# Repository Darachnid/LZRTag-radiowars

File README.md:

# [LZRTag](https://hackaday.io/project/160804-lzrtag-flexible-diy-lasertag)

### ESP32-Based Lasertag

Ever wanted to set up your own system of Lasertag?
Interested in having an easily modifiable system to create your own gamemodes and styles with?
Or just looking for a cool project to try out?
Well, why not take a spin at this!

*Note:* This project is not in serious development. I (Xasin) take no responsibility for what is done with this code, and I can't guarantee it'll do exactly what I tell it to (even if I try to give it treats >:c)
However, it is a fully functional system, if you know how to use it, and it has proven itself
to be pretty reliable and useful!

## The components
In order to have a functional game, you will need at least the following:
- Two or more soldered Lasertag Sets
- A WiFi access point or a newtwork of points throughout the arena.
- A MQTT Server, preferrably in the local network, to reduce ping.
- And a system running Ruby 2.4 or better, to run the Lasertag Backend and your gamemodes

## The Electronics
*Attention:* The electronics aren't necessarily beginner-friendly. I've designed them with components no smaller than a TSOP package or a 0805 resistor, but the newer versions of the hardware do include two QFN Packages - one for a optional IMU, so it can be left out, and one for a standard I2S audio chip, for which you can use any breakout board that supports 44100Hz, 16 bit playback. If you have a hot air gun,
definitely make use of it!

The electronics are based around the ESP32, a fairly cheap, powerful, WiFi and Bluetooth capable chip. The PCB includes all necessary support structures, including a battery charge circuit and a USB to UART converter to reprogram and debug the ESP.
It comes with the following hardware:
- The ESP32 plus beefy voltage regulation, ESD protection, etc. It ain't gonna break!
- A MAX I2S decoder + amplifier, for on-board, high quality audio.
- A LSM6D IMU, to detect movement, collisions, gestures, etc.
- Peripherals to receive and send IR Signals (documented here: TODO)
- Feedback in the shape of WS2812 LEDs and a vibration motor
- Trigger, Gun Select and Reload buttons.

The vest connection is exposed with a D-SUB connector, and I2C lines are available to make
more complex add-ons easier to achieve. There's also a I2C breakout connection on the PCB itself!

The Vest itself can be as simple as a couple of Vishay 40kHz IR receivers and WS2812 LEDs, but
there is a connection for vest-specific haptic feedback, and via the I2C connection it's easy to add
more complex features.

To solder one, check out the Aisler project here: https://aisler.net/p/QLILZEMV
Or head to the "Electronics" folder and generate your own Gerber files!

## The Casing
The 3D printed casing I designed is totally optional - the electronics can be easily fitted into any other casing, provided it has space for a switch, a speaker and a couple of LEDs!
However, if you do want to print it out, there's the Fusion360 page here: https://a360.co/2Lbm2zJ

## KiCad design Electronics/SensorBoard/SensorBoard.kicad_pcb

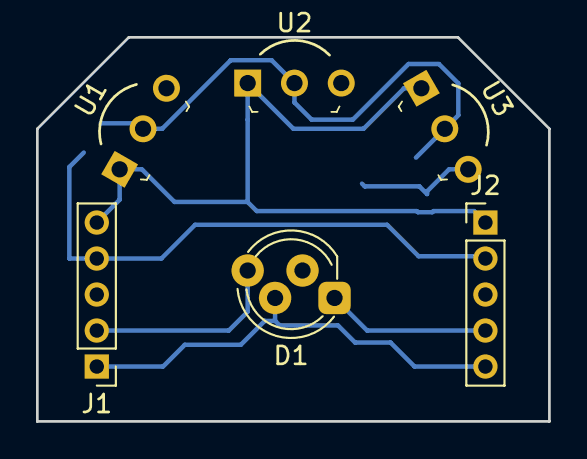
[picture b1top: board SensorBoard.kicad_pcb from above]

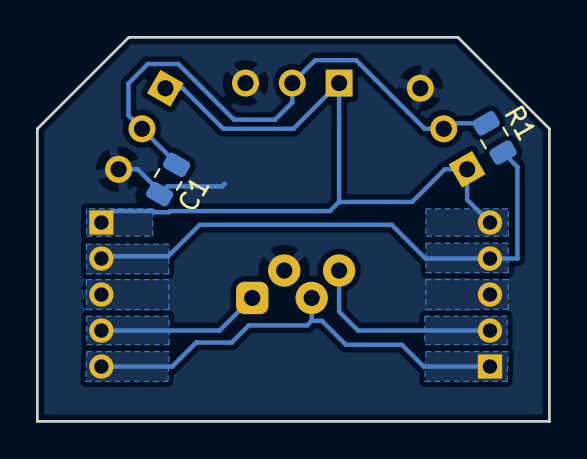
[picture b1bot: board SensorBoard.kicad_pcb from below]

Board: 2 copper layers, 28.4 x 21.3 mm, 8 parts (2 on the bottom side), 7 nets.

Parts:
C1: C_Small; C_0805_2012Metric
D1: NeoPixel_THT; LED_D5.0mm-4_RGB_Staggered_Pins
J1, J2: Conn_01x05_Male; PinHeader_1x05_P2.00mm_Vertical
R1: R_Small; R_0805_2012Metric
U1, U2, U3: TSSP58038; TO-92-3_Formed_Leads

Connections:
+3V3: J1.4, J2.2, R1.2
+BATT: D1.3, J1.1, J2.5
GND: C1.2, D1.2, J1.3, J2.3, U1.3, U2.3, U3.3
unnamed: C1.1, R1.1, U1.2, U2.2, U3.2
unnamed: D1.1, J2.4
unnamed: D1.4, J1.2
unnamed: J1.5, J2.1, U1.1, U2.1, U3.1

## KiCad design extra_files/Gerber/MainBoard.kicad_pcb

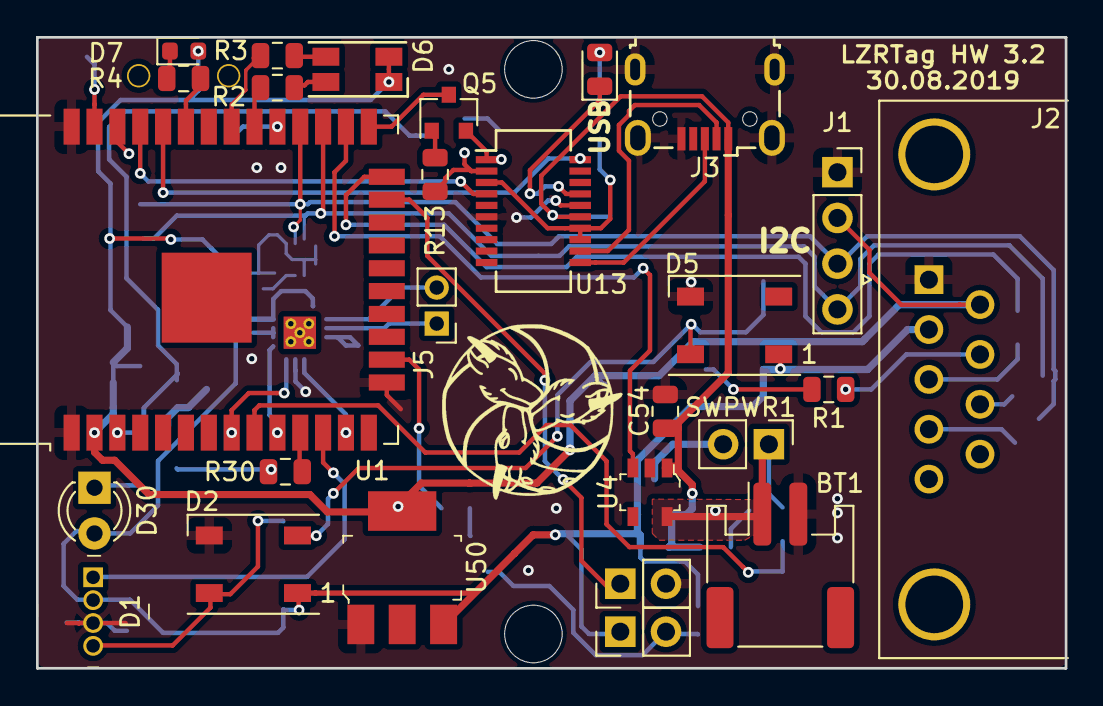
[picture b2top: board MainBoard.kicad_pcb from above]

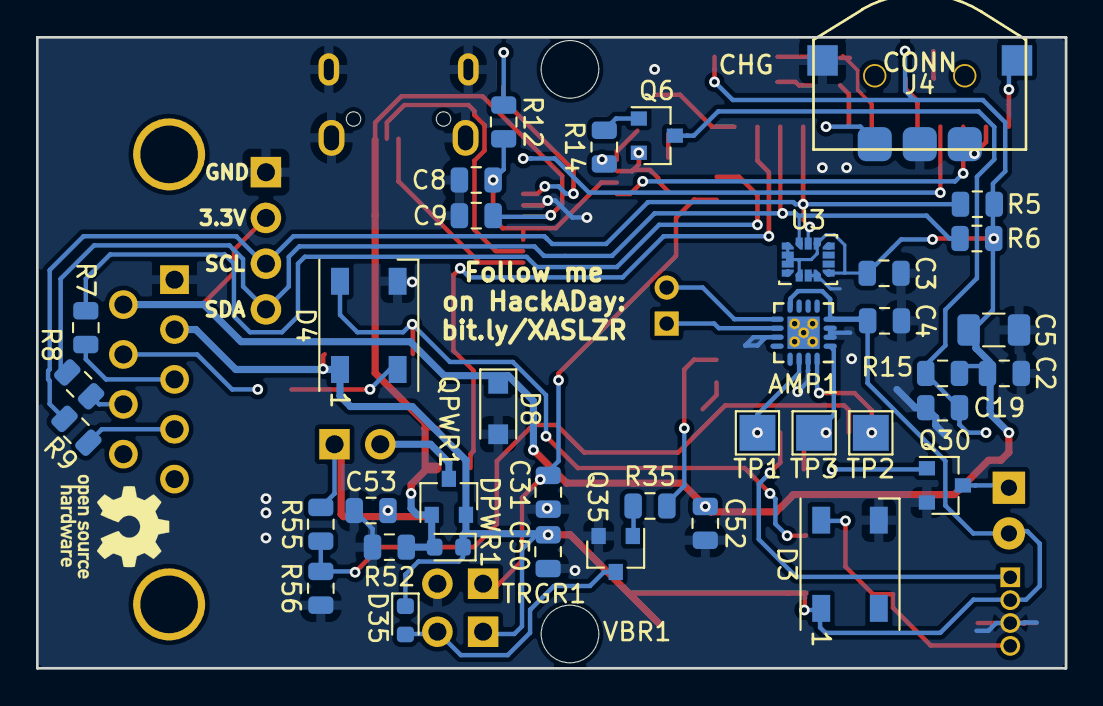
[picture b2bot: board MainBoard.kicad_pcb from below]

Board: 2 copper layers, 57.2 x 35.1 mm, 70 parts (40 on the bottom side), 53 nets.

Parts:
AMP1: MAX98357A; QFN-16-1EP_3x3mm_P0.5mm_EP2.7x2.7mm_ThermalVias
BT1: Battery_Cell; JST_PH_S2B-PH-SM4-TB_1x02-1MP_P2.00mm_Horizontal
C2, C8, C31: 150nF; C_0805_2012Metric
C3: 0.1uF; C_0805_2012Metric
C4, C9, C52, C53: 10uF; C_0805_2012Metric
C5: 47uF; C_1206_3216Metric
C19: 100nF; C_0805_2012Metric
C50, C54: 1uF; C_0805_2012Metric
D1: COM-12999; LED_RGB_WP154A4SUREQBFZGC
D2, D3, D4, D5: WS2812B; LED_WS2812B_PLCC4_5.0x5.0mm_P3.2mm
D6: LED_Dual_AACC; LED_RGB_1210
D7: LED; LED_0603_1608Metric
D8: D_Zener_ALT; D_SOD-123F
D30: SFH4346; LED_D3.0mm_IRBlack
D35: D_Schottky; D_0603_1608Metric
DPWR1: D_Schottky; D_0603_1608Metric
DUSB1: LED; LED_0805_2012Metric
H1, H2: MountingHole; MountingHole_3.2mm_M3_DIN965
H3: MountingHole; KiCad-Logo_5mm_SolderMask
H4: MountingHole; OSHW-Logo_5.7x6mm_SilkScreen
H6: MountingHole; DragonIcon
J1: Conn_01x04_Female; PinSocket_1x04_P2.54mm_Vertical
J2: DB9_Female; DSUB-9_Female_Horizontal_P2.77x2.84mm_EdgePinOffset4.94mm_H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
J3: USB_B_Micro; USB_Micro-B_Wuerth_629105150521
J4: Conn_01x04_Male; nav_switch_COM_08184
J5: Conn_01x02_Male; PinHeader_1x02_P2.00mm_Vertical
Q5, Q6: Q_NPN_BEC; SOT-23
Q30, Q35: PMBT2222A; SOT-23
QPWR1: IRLML6402; SOT-23
R1, R4, R7, R8, R9, R12, R30: 220; R_0805_2012Metric
R2, R3: 220R; R_0805_2012Metric
R5, R6, R35: 2.2k; R_0805_2012Metric
R13, R14, R15: R_Small; R_0805_2012Metric
R52: 10k; R_0805_2012Metric
R55: 100k; R_0805_2012Metric
R56: 200k; R_0805_2012Metric
SWPWR1: SW_SPST; PinHeader_1x02_P2.54mm_Vertical
TP1, TP2, TP3: TestPoint; TestPoint_Pad_2.0x2.0mm
TRGR1: SW_Push; PinHeader_1x02_P2.54mm_Vertical
U1: ESP32-WROOM-32
U3: LSM6DS3; LGA-14_3x2.5mm_P0.5mm_LayoutBorder3x4y
U4: MAX1555EZK_T; SOT-753
U13: FT231XS; SSOP-20_3.9x8.7mm_P0.635mm
U50: AP2114H-3_3TRG1; SOT-223
VBR1: Motor_DC_ALT; PinHeader_1x02_P2.54mm_Vertical

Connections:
+3V3: C2.1, C3.2, C5.2, C52.1, D6.1, D6.2, D7.2, D8.1, J1.2, J2.6, R5.1, R6.1, R15.1, U1.2, U3.1, U3.2, U3.3, U3.5, U3.8, U3.12, U50.4
+BATT: AMP1.4, AMP1.8, C4.1, C50.1, D1.2, D2.1, D3.1, D4.1, D5.1, D30.2, D35.1, DPWR1.1, J2.2, QPWR1.2, U50.3, VBR1.1
/AUDIO: AMP1.1, TP3.1, U1.10
/BCLK: AMP1.16, TP2.1, U1.8
/CHG_G: R3.2, U1.31
/CHG_R: R2.2, U1.30
/CHG_STAT: U1.26, U4.3
/CONN_IND: R4.2, U1.33
/CTRL_BACK: J4.1, U1.29
/CTRL_DOWN: J4.4, U1.37
/CTRL_FWD: J4.3, U1.36
/E>U: U1.35, U13.4
/GPIO0: Q5.3, U1.25
/IR_IN: R7.2, U1.24
/IR_OUT: R30.2, U1.11
/LED_1: D1.1, U1.12
/LED_2: D4.2, R1.2
/LRCLK: AMP1.14, TP1.1, U1.13
/PowerHandling/B_Raw+: BT1.1, C53.1, R55.1, SWPWR1.1, U4.5
/RESET: C19.1, Q6.3, R15.2, U1.3
/TRIGGER: C31.1, TRGR1.1, U1.23
/U>E: U1.34, U13.20
/USB Connection/+5V_USB: C9.2, C54.1, DPWR1.2, J3.1, QPWR1.1, R52.1, U4.1, U13.15
/USB Connection/USB3.3: C8.2, R12.1, U13.3, U13.13, U13.14
/VBRT: R35.2, U1.16
/V_SENSE: R55.2, R56.1, U1.9
GND: AMP1.2, AMP1.3, AMP1.11, AMP1.15, BT1.2, C2.2, C3.1, C4.2, C5.1, C8.1, C9.1, C19.2, C31.2, C50.2, C52.2, C53.2, C54.2, D1.3, D2.3, D3.3, D4.3, D5.3, D8.2, J1.1, J2.1, J3.5, J3.6, J4.2, Q30.2, Q35.2, R52.2, R56.2, TRGR1.2, U1.1, U1.15, U1.38, U3.6, U3.7, U4.2, U13.6, U13.16, U50.1
unnamed: AMP1.9, J5.2
unnamed: AMP1.10, J5.1
unnamed: D1.4, D2.4, D3.4
unnamed: D2.2, D4.4, D5.4
unnamed: D6.3, R3.1
unnamed: D6.4, R2.1
unnamed: D7.1, R4.1
unnamed: D30.1, Q30.3
unnamed: D35.2, Q35.3, VBR1.2
unnamed: DUSB1.1, U13.17
unnamed: DUSB1.2, R12.2
unnamed: J2.3, R7.1
unnamed: J2.4, R9.1
unnamed: J2.7, R1.1
unnamed: J2.8, R8.1
unnamed: J3.2, U13.12
unnamed: J3.3, U13.11
unnamed: Q5.1, R13.1
unnamed: Q5.2, R14.2, U13.1
unnamed: Q6.1, R14.1
unnamed: Q6.2, R13.2, U13.2
unnamed: Q30.1, R30.1
unnamed: Q35.1, R35.1
unnamed: QPWR1.3, SWPWR1.2
SCL: J1.3, R5.2, R9.2, U1.28, U3.13
SDA: J1.4, R6.2, R8.2, U1.27, U3.14

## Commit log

2023-12-16 add files via upload from hackaday, etc
2023-12-16 added gerber exports for pcb printing
2023-12-17 unzip
